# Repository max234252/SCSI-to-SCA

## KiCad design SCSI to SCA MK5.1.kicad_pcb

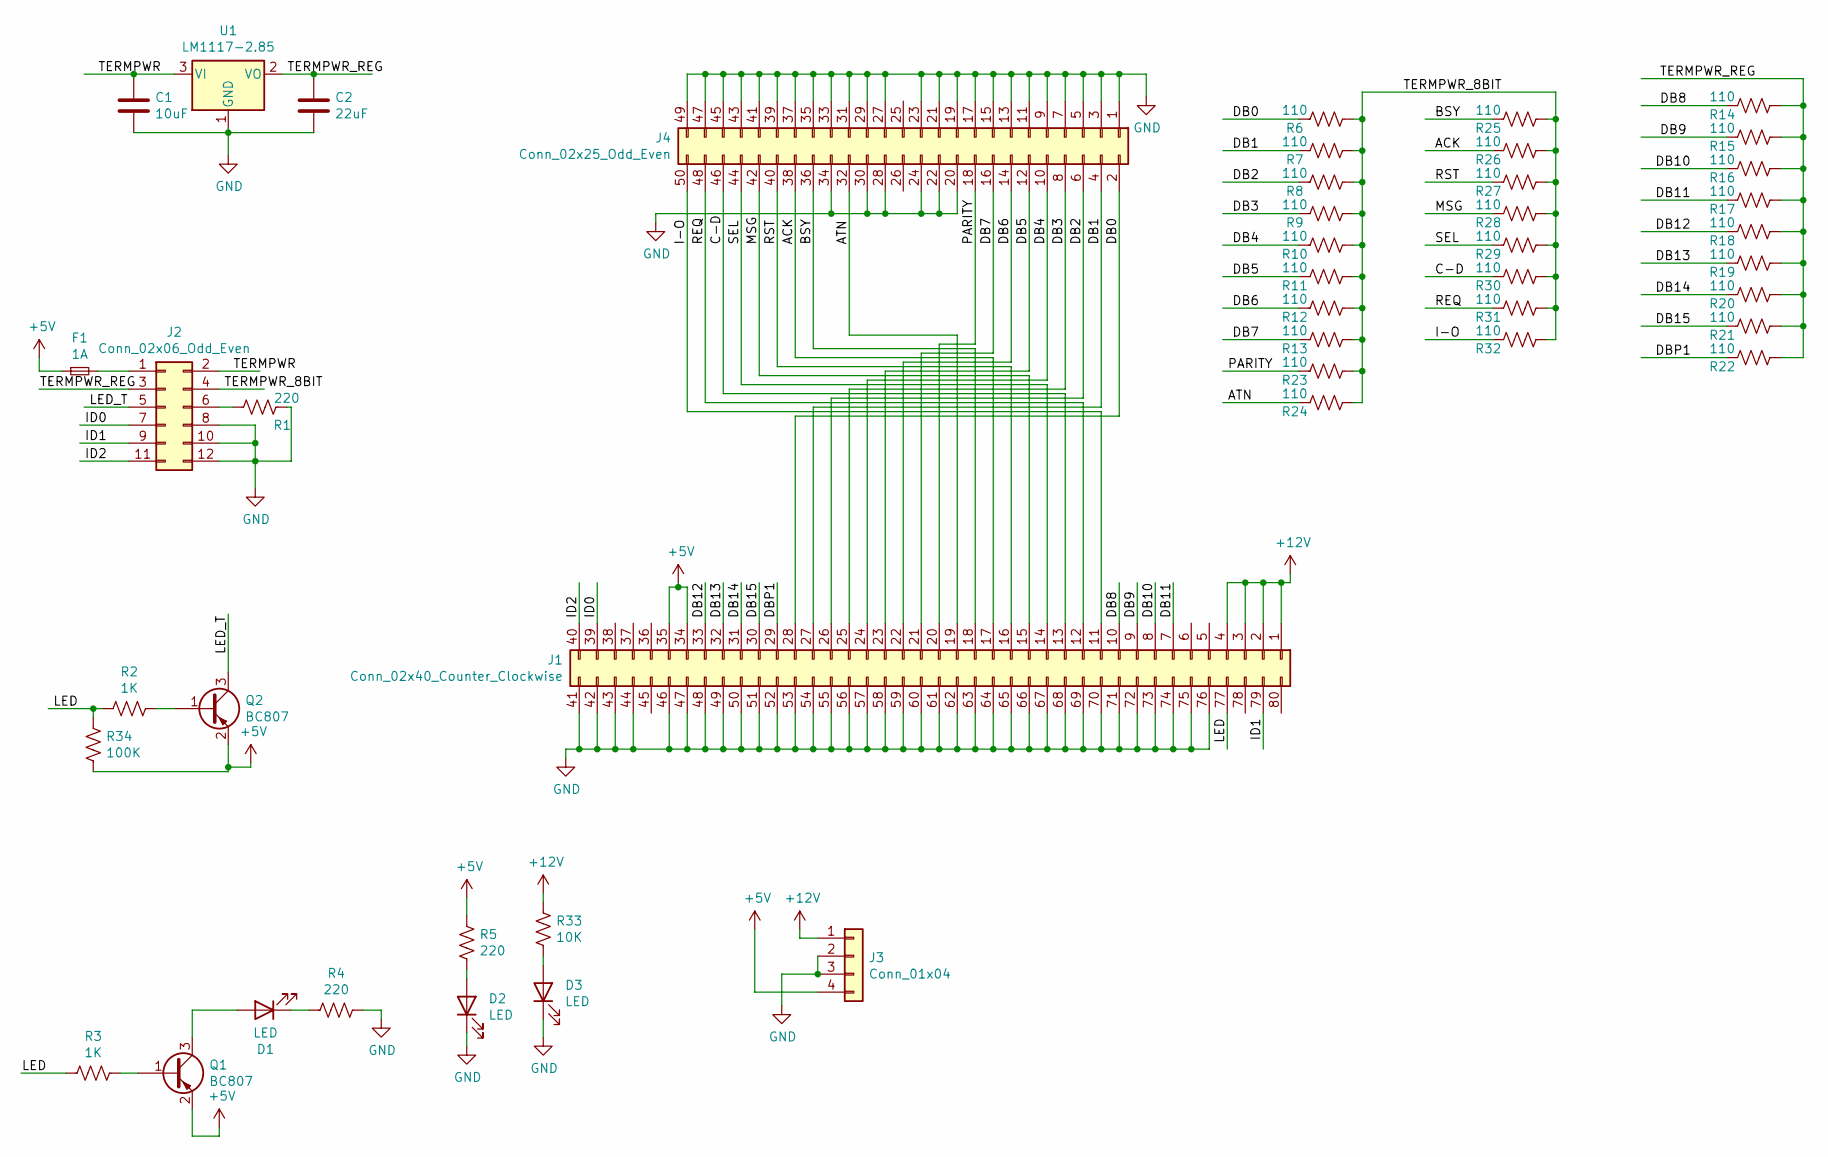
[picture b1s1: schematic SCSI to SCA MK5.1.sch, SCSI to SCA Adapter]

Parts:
C1: 10uF; C_0805_2012Metric
C2: 22uF; C_0805_2012Metric
D1, D2, D3: LED; LED_0603_1608Metric
F1: 1A; Fuse_1206_3216Metric
J1: Conn_02x40_Counter_Clockwise; 1734101-8
J2: Conn_02x06_Odd_Even; PinHeader_2x06_P2.54mm_Vertical
J3: Conn_01x04; TE_MATE-N-LOK_350211-1_1x04_P5.08mm_Vertical
J4: Conn_02x25_Odd_Even; IDC-Header_2x25_P2.54mm_Vertical
Q1, Q2: BC807; SOT-323_SC-70
R1, R4, R5: 220; R_0603_1608Metric
R2, R3: 1K; R_0603_1608Metric
R6, R7, R8, R9, R10, R11, R12, R13, R14, R15, R16, R17, R18, R19, R20, R21, R22, R23, R24, R25, R26, R27, R28, R29, R30, R31, R32: 110; R_0805_2012Metric
R33: 10K; R_0603_1608Metric
R34: 100K; R_0603_1608Metric
U1: LM1117-2.85; SOT-223-3_TabPin2

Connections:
+5V: F1.1, J1.34, J1.35, J3.4, Q1.2 (E), Q2.2 (E), R5.1, R34.2
+12V: J1.1, J1.2, J1.3, J1.4, J3.1, R33.1
/ACK: J1.17, J4.38, R26.2
/ATN: J1.19, J4.32, R24.2
/BSY: J1.18, J4.36, R25.2
/C-D: J1.13, J4.46, R30.2
/DB0: J1.28, J4.2, R6.2
/DB1: J1.27, J4.4, R7.2
/DB2: J1.26, J4.6, R8.2
/DB3: J1.25, J4.8, R9.2
/DB4: J1.24, J4.10, R10.2
/DB5: J1.23, J4.12, R11.2
/DB6: J1.22, J4.14, R12.2
/DB7: J1.21, J4.16, R13.2
/DB8: J1.10, R14.2
/DB9: J1.9, R15.2
/DB10: J1.8, R16.2
/DB11: J1.7, R17.2
/DB12: J1.33, R18.2
/DB13: J1.32, R19.2
/DB14: J1.31, R20.2
/DB15: J1.30, R21.2
/DBP1: J1.29, R22.2
/I-O: J1.11, J4.50, R32.2
/ID0: J1.39, J2.7
/ID1: J1.79, J2.9
/ID2: J1.40, J2.11
/LED: J1.77, R2.2, R3.2, R34.1
/LED_T: J2.5, Q2.3 (C)
/MSG: J1.15, J4.42, R28.2
/PARITY: J1.20, J4.18, R23.2
/REQ: J1.12, J4.48, R31.2
/RST: J1.16, J4.40, R27.2
/SEL: J1.14, J4.44, R29.2
/TERMPWR: C1.1, J2.2, U1.3 (VI)
/TERMPWR_8BIT: J2.4, R6.1, R7.1, R8.1, R9.1, R10.1, R11.1, R12.1, R13.1, R23.1, R24.1, R25.1, R26.1, R27.1, R28.1, R29.1, R30.1, R31.1, R32.1
/TERMPWR_REG: C2.1, J2.3, R14.1, R15.1, R16.1, R17.1, R18.1, R19.1, R20.1, R21.1, R22.1, U1.2 (VO)
GND: C1.2, C2.2, D2.1 (K), D3.1 (K), J1.41, J1.42, J1.43, J1.44, J1.46, J1.47, J1.48, J1.49, J1.50, J1.51, J1.52, J1.53, J1.54, J1.55, J1.56, J1.57, J1.58, J1.59, J1.60, J1.61, J1.62, J1.63, J1.64, J1.65, J1.66, J1.67, J1.68, J1.69, J1.70, J1.71, J1.72, J1.73, J1.74, J1.75, J1.76, J2.8, J2.10, J2.12, J3.2, J3.3, J4.1, J4.3, J4.5, J4.7, J4.9, J4.11, J4.13, J4.15, J4.17, J4.19, J4.20, J4.21, J4.22, J4.23, J4.24, J4.27, J4.28, J4.29, J4.30, J4.31, J4.33, J4.34, J4.35, J4.37, J4.39, J4.41, J4.43, J4.45, J4.47, J4.49, R1.2, R4.1, U1.1 (GND)
unnamed: D1.1 (K), R4.2
unnamed: D1.2 (A), Q1.3 (C)
unnamed: D2.2 (A), R5.2
unnamed: D3.2 (A), R33.2
unnamed: F1.2, J2.1
unnamed: J2.6, R1.1
unnamed: Q1.1 (B), R3.1
unnamed: Q2.1 (B), R2.1

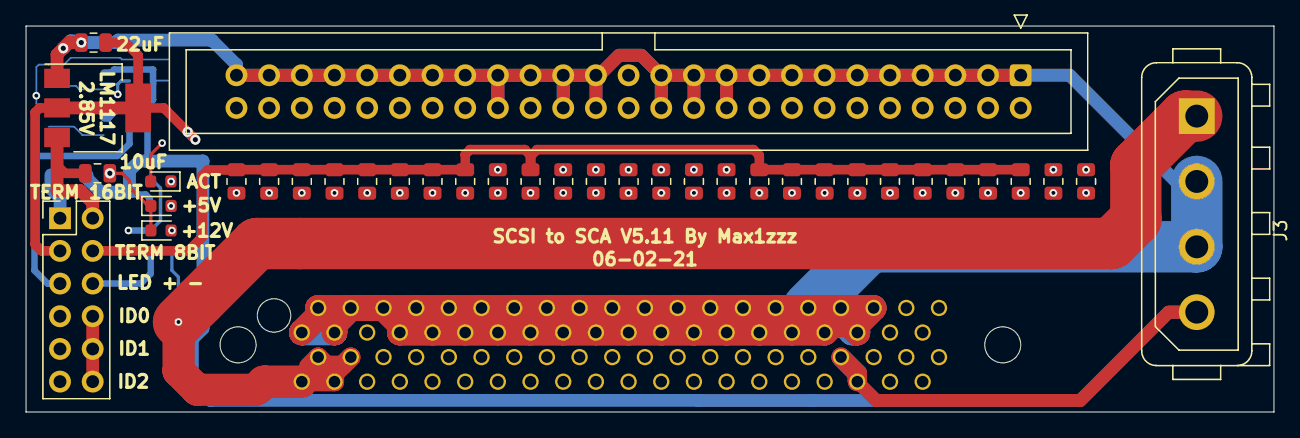
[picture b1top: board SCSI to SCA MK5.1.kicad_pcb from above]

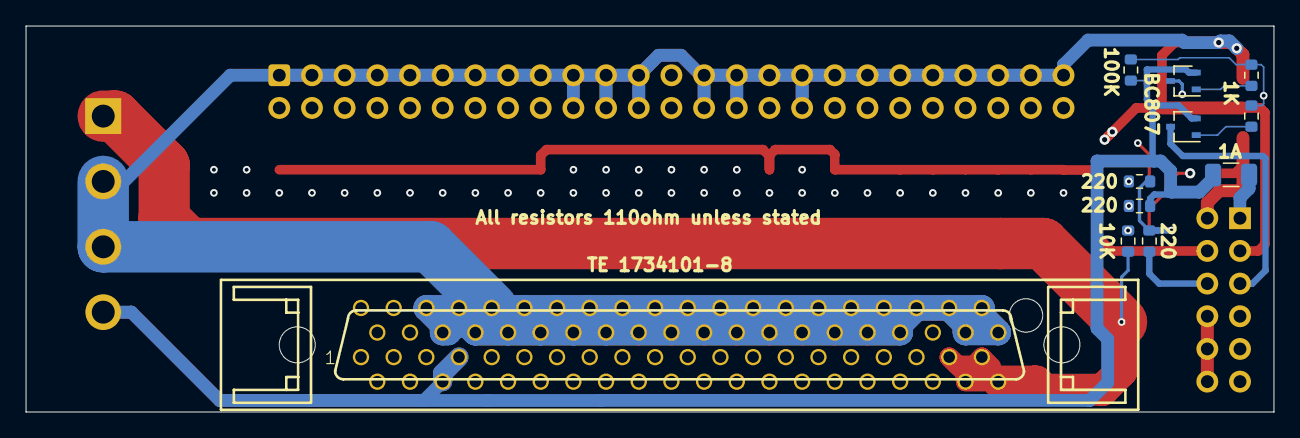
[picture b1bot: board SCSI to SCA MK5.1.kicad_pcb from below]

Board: 4 copper layers, 97.0 x 30.0 mm, 47 parts (11 on the bottom side), 46 nets.
